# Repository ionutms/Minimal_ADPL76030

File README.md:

# Minimal_ADPL76030

## Overview

This repository contains a minimal KiCad design project for the Analog Devices ADPL76030, a synchronous 4-switch buck-boost DC/DC controller. The project includes schematic designs and PCB layout files for implementing this versatile power supply controller.

## Disclaimer

> [!NOTE]
> This project is provided "as is" and without any warranty, express or implied. For more details, please see the [LICENSE](LICENSE) file.

## About the ADPL76030

The ADPL76030 from Analog Devices is a high-efficiency synchronous 4-switch buck-boost DC-to-DC controller. It can regulate output voltage and current from an input voltage that can be above, below, or equal to the output voltage.

Key features include:

- **Wide Input Voltage Range:** 4V to 55V.
- **High Efficiency:** Up to 95% at 1.4 MHz.
- **Spread Spectrum Frequency Modulation:** For low EMI.
- **Fault Protection:** Includes various protection features.
- **Current Monitoring:** Provides current monitoring capabilities.
- **Package:** Available in a 28-lead LFCSP package.

## Project Structure

```
minimal_adpl76030/
├── minimal_adpl76030.kicad_pro       # Project configuration file
├── minimal_adpl76030.kicad_sch       # Main schematic file
├── minimal_adpl76030.kicad_pcb       # PCB layout file
├── fp-lib-table                    # Footprint library table
├── sym-lib-table                   # Symbol library table
├── docs/                           # Documentation files
│   ├── bom/                        # Bill of Materials
│   │   └── minimal_adpl76030_ibom.html # Interactive BOM file
│   ├── pictures/                   # Images and photos
│   │   ├── 1_minimal_adpl76030_side.png
│   │   ├── 2_minimal_adpl76030_top.png
│   │   ├── 3_minimal_adpl76030_bottom.png
│   │   ├── 4_minimal_adpl76030_left.png
│   │   └── 5_minimal_adpl76030_right.png
│   └── schematics/                 # Schematic PDF exports
│       └── minimal_adpl76030_schematics.pdf
└── KiCAD_Symbols_Generator/        # Submodule for symbol generation from CSV data
```

## Project Features

This design provides a minimal implementation of the ADPL76030 with:

- Proper power supply connections
- Buck-boost functionality
- Standard footprint for the 28-pin LFCSP package

## Getting Started

### Prerequisites

- [KiCad EDA](https://www.kicad.org/) version 9.0 or later installed on your system
- Git (for cloning the repository and submodule management)

### Opening the Project

1. **Clone the repository** (including submodules):
   ```bash
   git clone --recursive https://github.com/ionutms/Minimal_ADPL76030.git
   ```
   
   If you've already cloned the repository without submodules, initialize them with:
   ```bash
   git submodule init
   git submodule update
   ```

2. **Open the project in KiCad**:
   - Launch KiCad
   - Click "Open Existing Project"
   - Navigate to the cloned repository folder
   - Select the `minimal_adpl76030.kicad_pro` file

3. **Explore the design**:
   - Open the schematic editor to view the circuit design
   - Open the PCB editor to view the board layout
   - Review the symbol and footprint libraries used in the design

### Project Files

- **Main schematic**: `minimal_adpl76030.kicad_sch` - Contains the primary circuit design with the ADPL76030 and support components
- **PCB layout**: `minimal_adpl76030.kicad_pcb` - Physical board design file with proper component placement
- **Project configuration**: `minimal_adpl76030.kicad_pro` - KiCad project settings

## Dependencies

This project has the following dependencies:

### 1. KiCAD Symbols Generator

This repository uses [KiCAD_Symbols_Generator](https://github.com/ionutms/KiCAD_Symbols_Generator) as a submodule for custom symbol generation.

To initialize the submodule after cloning this repository:

```bash
git submodule update --init --recursive
```

### 2. 3D Models

This project requires the [3D_Models_Vault](https://github.com/ionutms/3D_Models_Vault) repository for 3D models.

#### Setup for KiCAD 9:

1. Clone the 3D models repository:
   ```bash
   git clone https://github.com/ionutms/3D_Models_Vault.git
   ```

2. In KiCAD 9, add an environment variable:
   - Variable name: `KICAD9_3D_MODELS_VAULT`
   - Variable value: Full path to where you cloned the 3D_Models_Vault repository

## Usage

After setting up the dependencies, open the project in KiCad 9 to access all features including the 3D models.

## Symbol Generator Submodule

This project includes the KiCAD_Symbols_Generator as a submodule, which provides tools for generating KiCad symbols from CSV data files. For more information on using this tool, see the [KiCAD_Symbols_Generator documentation](minimal_adpl76030/KiCAD_Symbols_Generator/README.md).

## Documentation

The `docs` folder contains:
- Schematic PDF exports
- Images and photos of the design

## Visuals

The following images showcase the PCB design from different perspectives:

*Top View of the PCB*

*Side View of the PCB*

*Bottom View of the PCB*

*Left View of the PCB*

*Right View of the PCB*

## License

This project is licensed under the MIT License - see the [LICENSE](LICENSE) file for details.

## References

- [ADPL76030 Datasheet](https://www.analog.com/media/en/technical-documentation/data-sheets/adpl76030.pdf)
- [KiCad EDA](https://www.kicad.org/)

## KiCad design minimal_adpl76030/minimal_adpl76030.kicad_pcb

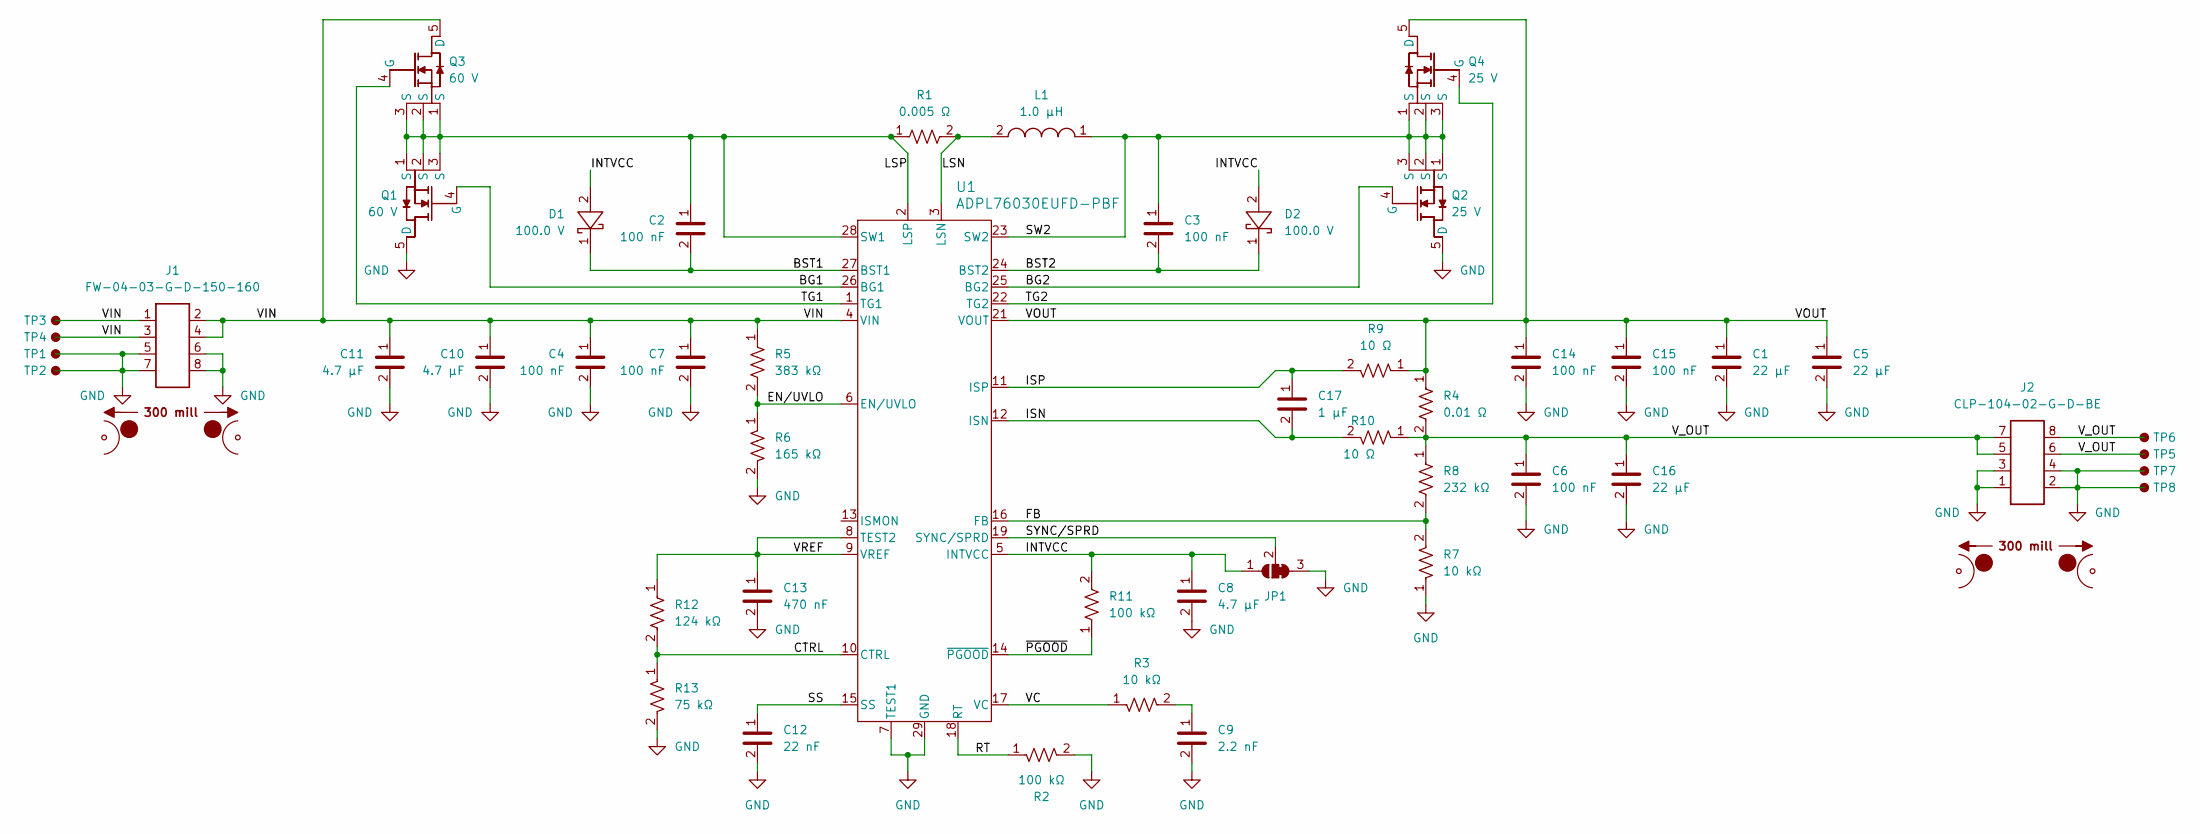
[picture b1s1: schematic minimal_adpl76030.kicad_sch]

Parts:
C1, C5, C16: 22 µF; C_1206_3216Metric; Tolerance 10%; Voltage Rating 25V; MPN CL31A226KAHNNNE
C2, C3, C4, C6, C7, C14, C15: 100 nF; C_0402_1005Metric; Tolerance 10%; Voltage Rating 50V; MPN GCM155R71H104KE02D
C8: 4.7 µF; C_0603_1608Metric; Tolerance 10%; Voltage Rating 10V; MPN GRM188C71A475KE11D
C9: 2.2 nF; C_0402_1005Metric; Tolerance 10%; Voltage Rating 50V; MPN GCM155R71H222KA37D
C10, C11: 4.7 µF; C_1206_3216Metric; Tolerance 10%; Voltage Rating 50V; MPN CL31B475KBHNNN#
C12: 22 nF; C_0402_1005Metric; Tolerance 10%; Voltage Rating 50V; MPN GCM155R71H223KA55D
C13: 470 nF; C_0402_1005Metric; Tolerance 10%; Voltage Rating 10V; MPN GCM155C71A474KE36D
C17: 1 µF; C_0402_1005Metric; Tolerance 10%; Voltage Rating 16V; MPN C1005X6S1C105K050BC
D1, D2: 100.0 V; SOD323F; MPN BAT46WJ,115
J1: FW-04-03-G-D-150-160; Current Rating (A) 5.2; Voltage Rating (V) 300; MPN FW-04-03-G-D-150-160
J2: CLP-104-02-G-D-BE; Current Rating (A) 5.2; Voltage Rating (V) 300; MPN CLP-104-02-G-D-BE
JP1: SolderJumper_3_Open; SolderJumper-3_P1.3mm_Bridged_2_3_RoundedPad1.0x1.5mm_Numbe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
L1: 1.0 µH; 74437336; Tolerance ±20%; MPN 74437336010
MB1, MB2: mouse-bite-50mil-300mil
Q1, Q3: 60 V; TSDSON-8FL; MPN BSZ065N06LS5ATMA1
Q2, Q4: 25 V; TSDSON-8FL; MPN BSZ031NE2LS5ATMA1
R1: 0.005 Ω; R_2010_5025Metric; Tolerance 1%; MPN CRF2010-FZ-R005ELF
R2, R11: 100 kΩ; R_0402_1005Metric; Tolerance 1%; Voltage Rating 50V; MPN ERJ-2RKF1003X
R3, R7: 10 kΩ; R_0402_1005Metric; Tolerance 1%; Voltage Rating 50V; MPN ERJ-2RKF1002X
R4: 0.01 Ω; R_2010_5025Metric; Tolerance 1%; MPN CRF2010-FZ-R010ELF
R5: 383 kΩ; R_0402_1005Metric; Tolerance 1%; Voltage Rating 50V; MPN ERJ-2RKF3833X
R6: 165 kΩ; R_0402_1005Metric; Tolerance 1%; Voltage Rating 50V; MPN ERJ-2RKF1653X
R8: 232 kΩ; R_0402_1005Metric; Tolerance 1%; Voltage Rating 50V; MPN ERJ-2RKF2323X
R9, R10: 10 Ω; R_0402_1005Metric; Tolerance 1%; Voltage Rating 50V; MPN ERJ-2RKF10R0X
R12: 124 kΩ; R_0402_1005Metric; Tolerance 1%; Voltage Rating 50V; MPN ERJ-2RKF1243X
R13: 75 kΩ; R_0402_1005Metric; Tolerance 1%; Voltage Rating 50V; MPN ERJ-2RKF7502X
TP1, TP2, TP3, TP4, TP5, TP6, TP7, TP8: TestPoint; TestPoint_THTPad_Castelated
U1: ADPL76030EUFD-PBF; UFD_05-08-1712_ADI; MPN ADPL76030EUFD-PBF

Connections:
/BG1: Q1.4 (G), U1.26 (BG1)
/BG2: Q2.4 (G), U1.25 (BG2)
/BST1: C2.2, D1.1, U1.27 (BST1)
/BST2: C3.2, D2.1, U1.24 (BST2)
/CTRL: R12.2, R13.1, U1.10 (CTRL)
/EN/UVLO: R5.2, R6.1, U1.6 (EN/UVLO)
/FB: R7.2, R8.2, U1.16 (FB)
/INTVCC: C8.1, D1.2, D2.2, JP1.1 (A), R11.2, U1.5 (INTVCC)
/ISN: C17.2, R10.2, U1.12 (ISN)
/ISP: C17.1, R9.2, U1.11 (ISP)
/LSN: L1.2, R1.2, U1.3 (LSN)
/LSP: C2.1, Q1.1 (S), Q1.2 (S), Q1.3 (S), Q3.1 (S), Q3.2 (S), Q3.3 (S), R1.1, U1.2 (LSP), U1.28 (SW1)
/RT: R2.1, U1.18 (RT)
/SS: C12.1, U1.15 (SS)
/SW2: C3.1, L1.1, Q2.1 (S), Q2.2 (S), Q2.3 (S), Q4.1 (S), Q4.2 (S), Q4.3 (S), U1.23 (SW2)
/SYNC/SPRD: JP1.2 (C), U1.19 (SYNC/SPRD)
/TG1: Q3.4 (G), U1.1 (TG1)
/TG2: Q4.4 (G), U1.22 (TG2)
/VC: R3.1, U1.17 (VC)
/VIN: C4.1, C7.1, C10.1, C11.1, J1.1, J1.2, J1.3, J1.4, Q3.5 (D), R5.1, TP3.1, TP4.1, U1.4 (VIN)
/VOUT: C1.1, C5.1, C14.1, C15.1, Q4.5 (D), R4.1, R9.1, U1.21 (VOUT)
/VREF: C13.1, R12.1, U1.8 (TEST2), U1.9 (VREF)
/V_OUT: C6.1, C16.1, J2.5, J2.6, J2.7, J2.8, R4.2, R8.1, R10.1, TP5.1, TP6.1
/~PGOOD: R11.1, U1.14 (~PGOOD)
GND: C1.2, C4.2, C5.2, C6.2, C7.2, C8.2, C9.2, C10.2, C11.2, C12.2, C13.2, C14.2, C15.2, C16.2, J1.5, J1.6, J1.7, J1.8, J2.1, J2.2, J2.3, J2.4, JP1.3 (B), Q1.5 (D), Q2.5 (D), R2.2, R6.2, R7.1, R13.2, TP1.1, TP2.1, TP7.1, TP8.1, U1.7 (TEST1), U1.29 (GND)
unnamed: C9.1, R3.2

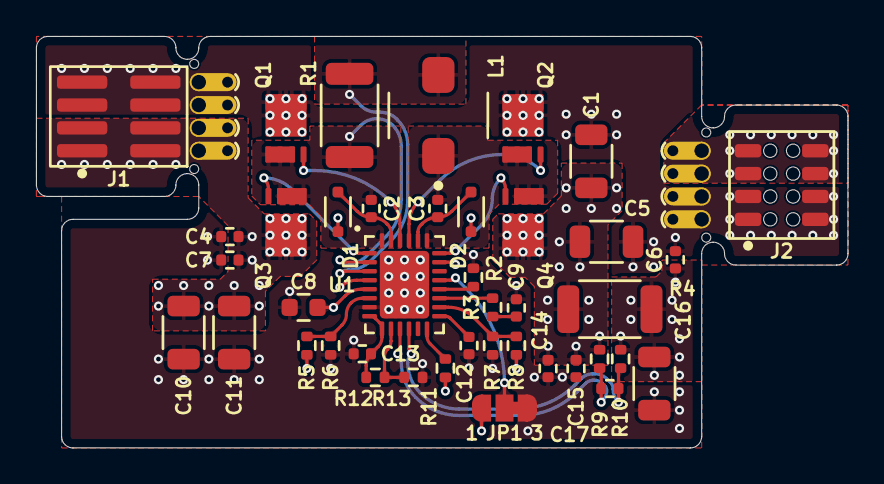
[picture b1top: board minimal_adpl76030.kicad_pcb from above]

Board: 4 copper layers, 45.1 x 22.9 mm, 51 parts (0 on the bottom side), 26 nets.

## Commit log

2025-09-28 Set up KiCAD project with initial schematic, PCB, and GitHub workflows
2025-09-28 Update KiCad documentation for minimal_adpl76030 (schematics and PCB renders)
2025-09-28 backup
2025-10-01 Update README.md with comprehensive documentation
2025-10-04 Update KiCAD configuration
2025-10-04 Add trigger-symbol-check workflow and update generate_kicad_jobs
2025-10-04 Update trigger-symbol-check workflow
2025-10-05 chore: update workflows and kicad config from central repository
2025-10-26 Update kicad-config.yml to adjust zoom and pan for better views
